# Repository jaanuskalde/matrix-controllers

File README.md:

matrix-controllers
==================

Stackable LED matrix controller boards

Tech-thing 2013

http://tech-thing.org

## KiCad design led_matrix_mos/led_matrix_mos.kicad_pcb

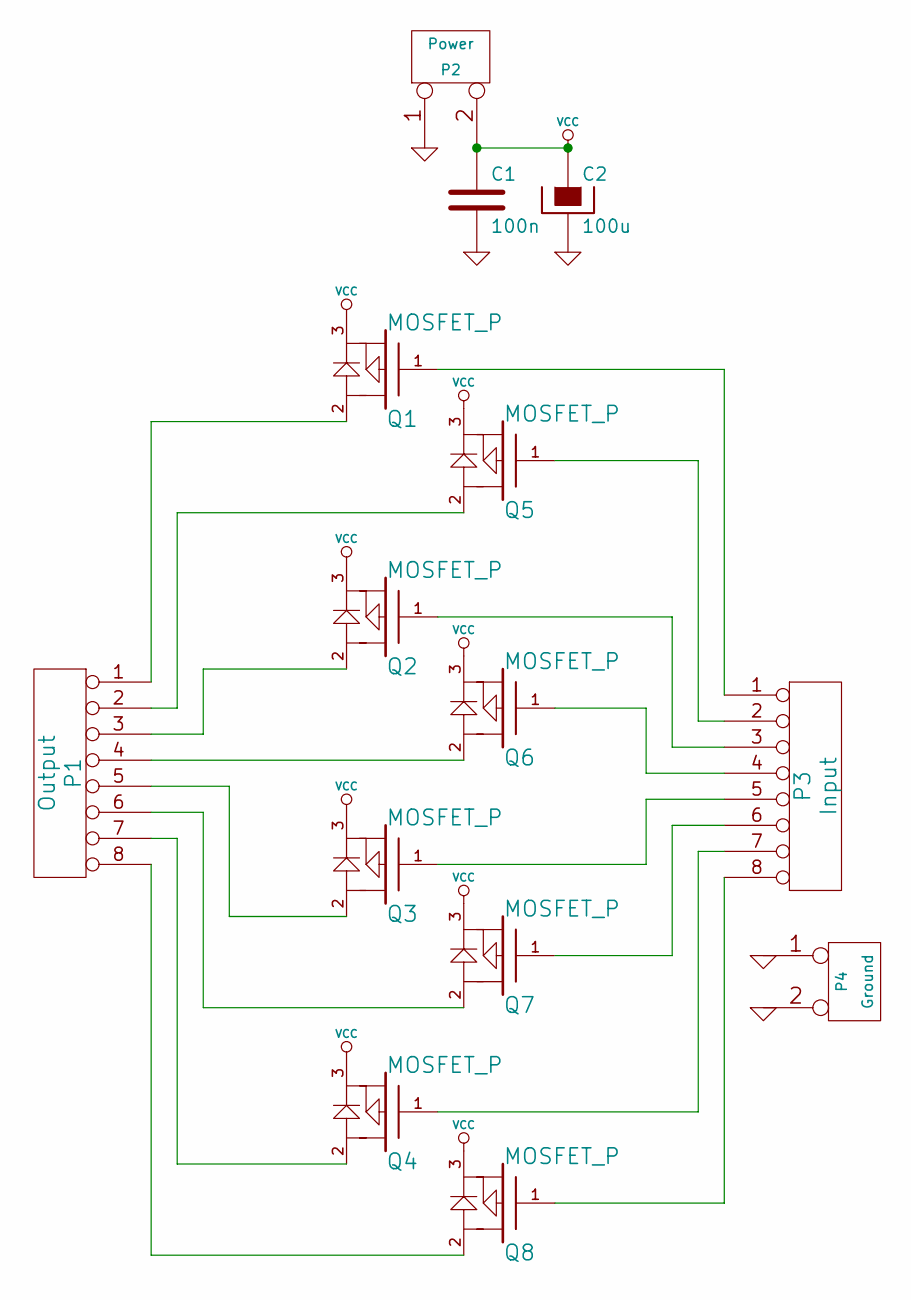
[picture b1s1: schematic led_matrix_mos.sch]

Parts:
C1: 100n
C2: 100u
P1: Output
P2: Power
P3: Input
P4: Ground
Q1, Q2, Q3, Q4, Q5, Q6, Q7, Q8: MOSFET_P

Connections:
GND: C1.2, C2.2, P2.1, P4.1, P4.2 (PM)
unnamed: P3.3, Q2.1 (G)
unnamed: P1.8, Q8.2 (D)
unnamed: P3.5, Q3.1 (G)
unnamed: P3.6, Q7.1 (G)
unnamed: P3.7, Q4.1 (G)
unnamed: P3.8, Q8.1 (G)
unnamed: P3.4, Q6.1 (G)
unnamed: P3.2, Q5.1 (G)
unnamed: P3.1, Q1.1 (G)
unnamed: P1.4, Q6.2 (D)
unnamed: P1.3, Q2.2 (D)
unnamed: P1.2, Q5.2 (D)
unnamed: P1.1, Q1.2 (D)
unnamed: P1.5, Q3.2 (D)
unnamed: P1.6, Q7.2 (D)
unnamed: P1.7, Q4.2 (D)
VCC: C1.1, C2.1, P2.2 (PM), Q1.3 (S), Q2.3 (S), Q3.3 (S), Q4.3 (S), Q5.3 (S), Q6.3 (S), Q7.3 (S), Q8.3 (S)

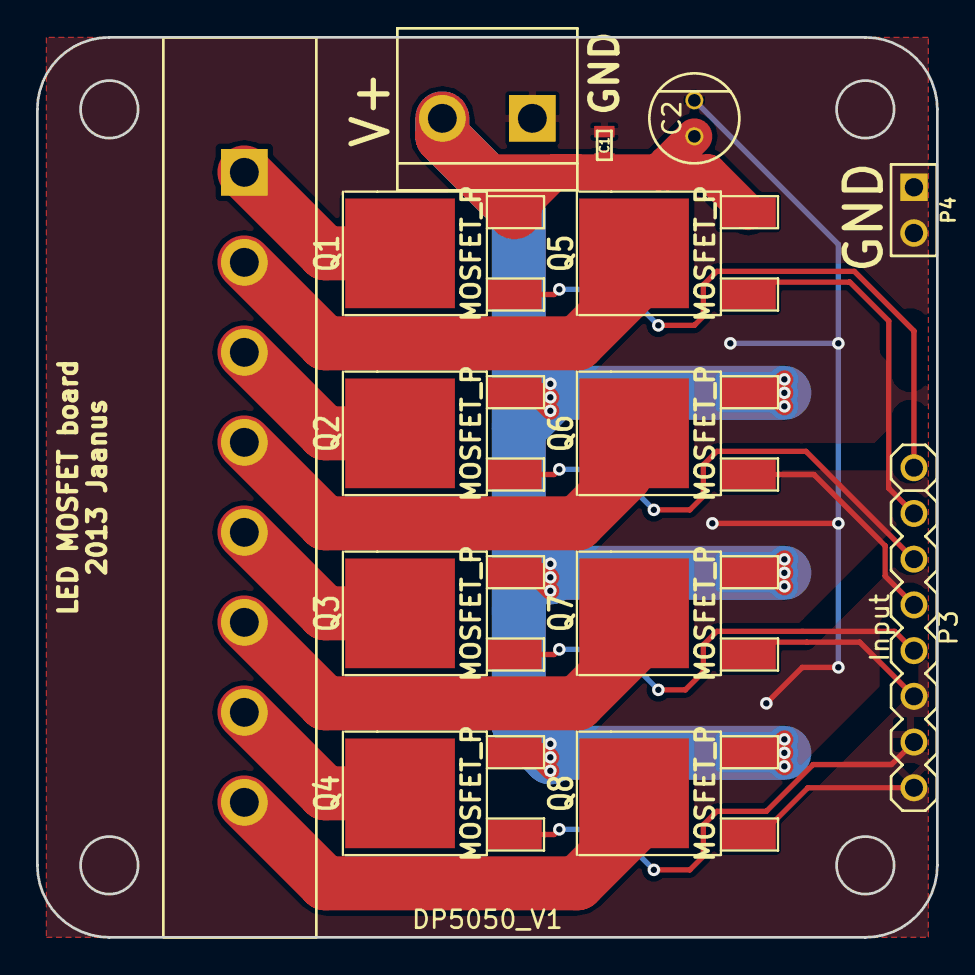
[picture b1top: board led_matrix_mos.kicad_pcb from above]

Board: 2 copper layers, 50.0 x 50.0 mm, 15 parts (0 on the bottom side), 18 nets.

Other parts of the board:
DP5050_V1: VAL**; DP5050_V1

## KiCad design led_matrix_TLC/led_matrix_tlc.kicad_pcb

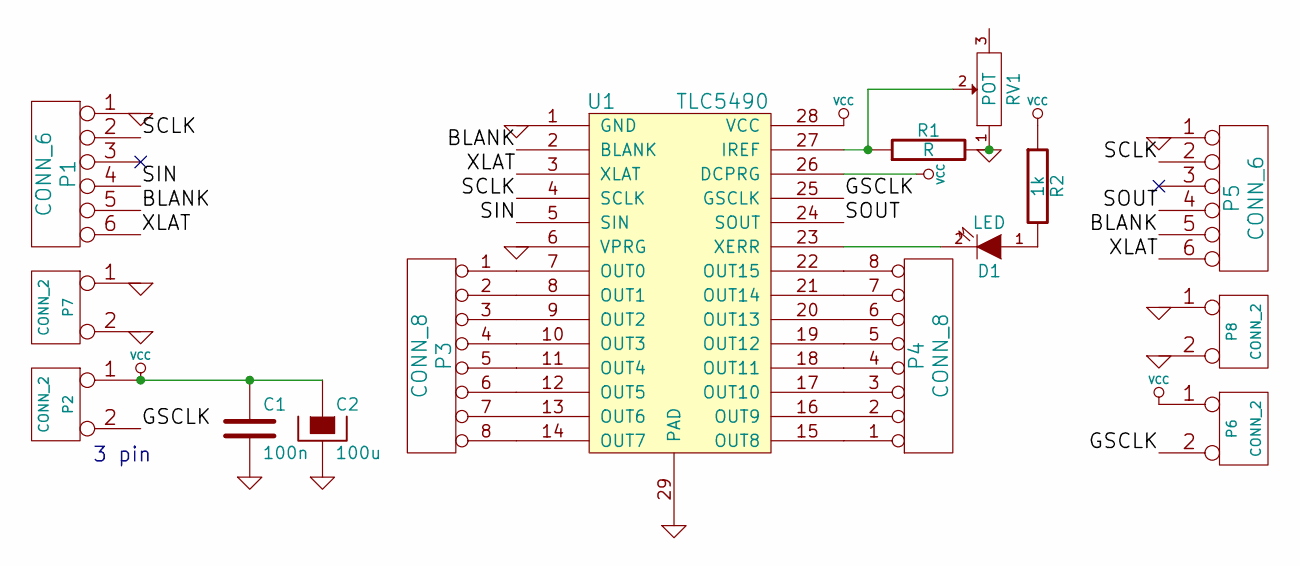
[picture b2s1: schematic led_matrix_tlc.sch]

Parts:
C1: 100n
C2: 100u
D1: LED
P1, P5: CONN_6
P2, P6, P7, P8: CONN_2
P3, P4: CONN_8
R1: R
R2: 1k
RV1: POT
U1: TLC5490

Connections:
/BLANK: P1.5, P5.5, U1.2 (BLANK)
/GSCLK: P2.2 (PM), P6.2 (PM), U1.25 (GSCLK)
/SCLK: P1.2, P5.2, U1.4 (SCLK)
/SIN: P1.4, U1.5 (SIN)
/SOUT: P5.4, U1.24 (SOUT)
/XLAT: P1.6, P5.6, U1.3 (XLAT)
GND: C1.2, C2.2, P1.1, P5.1, P7.1, P7.2 (PM), P8.1, P8.2 (PM), R1.2, RV1.1, U1.1 (GND), U1.6 (VPRG), U1.29 (PAD)
unnamed: P3.2, U1.8 (OUT1)
unnamed: D1.2 (K), U1.23 (XERR)
unnamed: P3.1, U1.7 (OUT0)
unnamed: P3.3, U1.9 (OUT2)
unnamed: P3.4, U1.10 (OUT3)
unnamed: P4.6, U1.20 (OUT13)
unnamed: P3.5, U1.11 (OUT4)
unnamed: P4.7, U1.21 (OUT14)
unnamed: P3.6, U1.12 (OUT5)
unnamed: P4.8, U1.22 (OUT15)
unnamed: P3.7, U1.13 (OUT6)
unnamed: R1.1, RV1.2, U1.27 (IREF)
unnamed: D1.1 (A), R2.2
unnamed: P4.4, U1.18 (OUT11)
unnamed: P3.8, U1.14 (OUT7)
unnamed: P4.1, U1.15 (OUT8)
unnamed: P4.2, U1.16 (OUT9)
unnamed: P4.3, U1.17 (OUT10)
unnamed: P4.5, U1.19 (OUT12)
VCC: C1.1, C2.1, P2.1, P6.1, R2.1, U1.26 (DCPRG), U1.28 (VCC)

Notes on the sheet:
3 pin

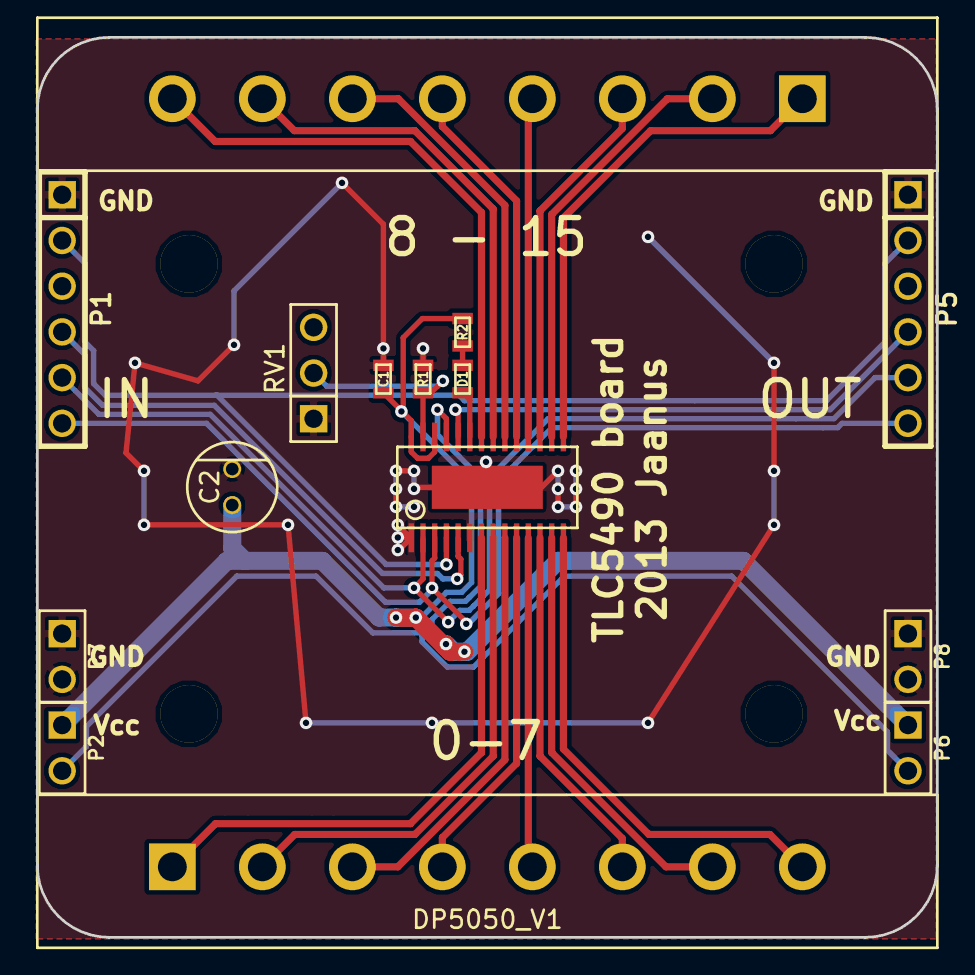
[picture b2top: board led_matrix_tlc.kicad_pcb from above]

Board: 2 copper layers, 50.0 x 50.0 mm, 20 parts (0 on the bottom side), 27 nets.

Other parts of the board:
DP5050_V1: VAL**; DP5050_no_holes
drill_3.2mm, drill_3.2mm#2, drill_3.2mm#3, drill_3.2mm#4: VAL**; drill_3.2mm

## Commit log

2014-10-19 schematics and boards
2014-10-19 readme update
